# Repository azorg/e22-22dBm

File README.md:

Simple E22-400M22S RF module development shield
===============================================

Kicad 6.0 PCB project

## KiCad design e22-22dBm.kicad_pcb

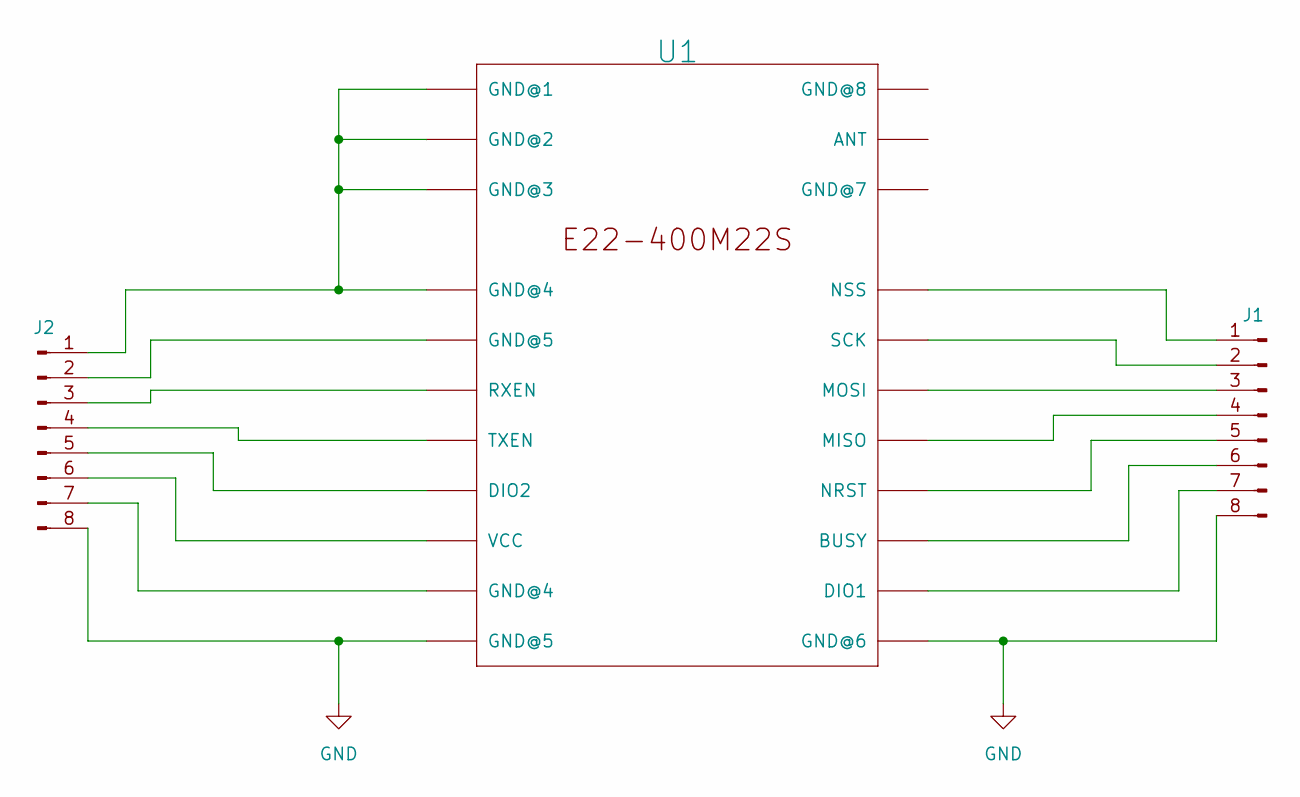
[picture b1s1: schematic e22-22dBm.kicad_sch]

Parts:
J1, J2: Conn_01x08_Male; PinHeader_1x08_P2.54mm_Vertical
U1: E22-400M22S

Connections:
GND: J1.8, J2.8, U1.11 (GND@5), U1.12 (GND@6)
unnamed: J1.1, U1.19 (NSS)
unnamed: J1.2, U1.18 (SCK)
unnamed: J1.3, U1.17 (MOSI)
unnamed: J1.4, U1.16 (MISO)
unnamed: J1.5, U1.15 (NRST)
unnamed: J1.6, U1.14 (BUSY)
unnamed: J1.7, U1.13 (DIO1)
unnamed: J2.1, U1.1 (GND@1), U1.2 (GND@2), U1.3 (GND@3), U1.4 (GND@4)
unnamed: J2.2, U1.5 (GND@5)
unnamed: J2.3, U1.6 (RXEN)
unnamed: J2.4, U1.7 (TXEN)
unnamed: J2.5, U1.8 (DIO2)
unnamed: J2.6, U1.9 (VCC)
unnamed: J2.7, U1.10 (GND@4)

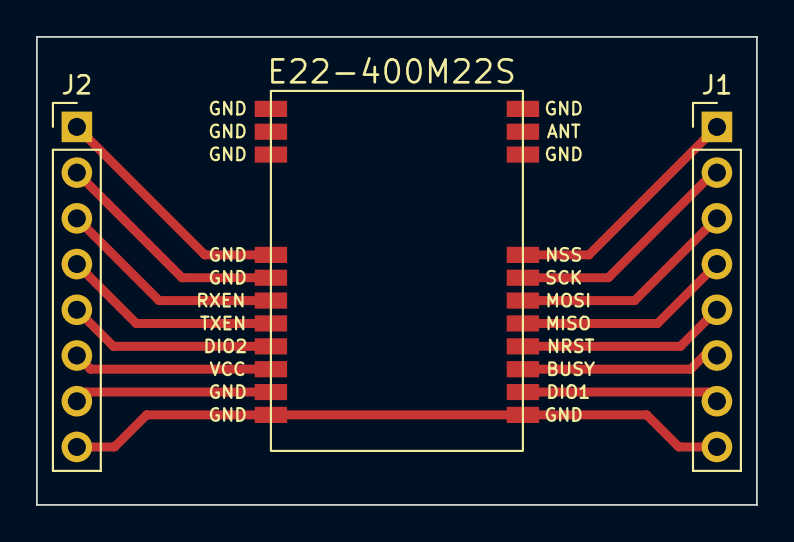
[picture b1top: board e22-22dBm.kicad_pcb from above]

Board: 2 copper layers, 40.0 x 26.0 mm, 3 parts (0 on the bottom side), 15 nets.

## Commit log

2023-01-17 some fix
